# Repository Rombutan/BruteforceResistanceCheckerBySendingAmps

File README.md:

# BruteforceResistanceCheckerBySendingAmps

Want to measure small resistance things like fuses or wires? You can either spend days making some fancy amplifier or just pump a few amps through the thing you wanna measure and voila. That's what this project is.

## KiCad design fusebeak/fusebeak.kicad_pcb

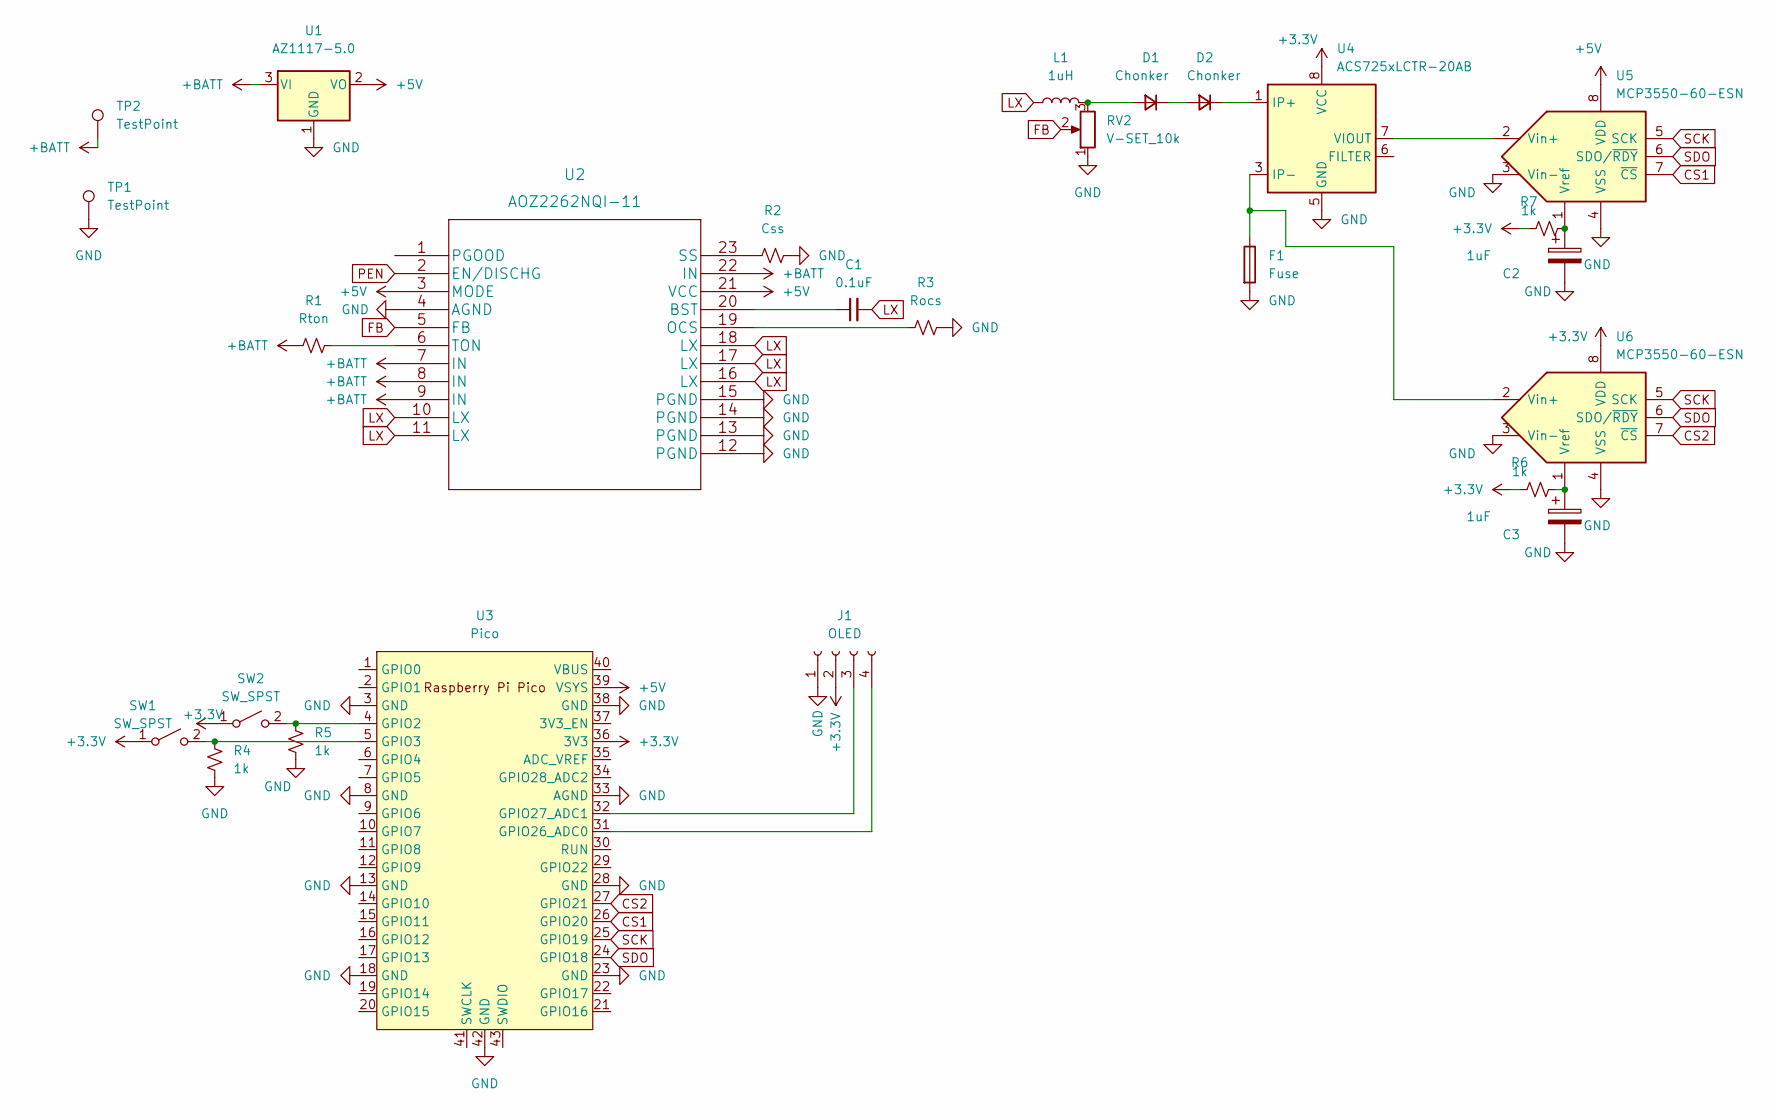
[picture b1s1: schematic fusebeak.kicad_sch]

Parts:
C1: 0.1uF; C_0402_1005Metric
C2, C3: 1uF; C_0402_1005Metric
D1, D2: Chonker; D_5KPW_P12.70mm_Horizontal
F1: Fuse; Fuseholder_Blade_ATO_Littelfuse_Pudenz_2_Pin
J1: OLED; PinHeader_1x04_P2.54mm_Vertical
L1: 1uH; L_7.3x7.3_H4.5
R1: Rton; R_0402_1005Metric
R2: Css; R_0402_1005Metric
R3: Rocs; R_0402_1005Metric
R4, R5, R6, R7: 1k; R_0402_1005Metric
RV2: V-SET_10k; Potentiometer_Bourns_3266Y_Vertical
SW1, SW2: SW_SPST; KSA_Tactile_SPST
TP1, TP2: TestPoint; TestPoint_Plated_Hole_D5.0mm
U1: AZ1117-5.0; SOT-223-3_TabPin2
U2: AOZ2262NQI-11
U3: Pico; RPi_Pico_SMD_TH
U4: ACS725xLCTR-20AB; SOIC-8_3.9x4.9mm_P1.27mm
U5, U6: MCP3550-60-ESN; SOIC-8-1EP_3.9x4.9mm_P1.27mm_EP2.29x3mm

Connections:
+3.3V: J1.2, R6.1, R7.1, SW1.1 (A), SW2.1 (A), U3.36 (3V3), U4.8 (VCC), U6.8 (VDD)
+5V: U1.2 (VO), U2.3 (MODE), U2.21 (VCC), U3.39 (VSYS), U5.8 (VDD)
+BATT: R1.1, TP2.1, U1.3 (VI), U2.7 (IN), U2.8 (IN), U2.9 (IN), U2.22 (IN)
CS1: U3.26 (GPIO20), U5.7 (~CS)
CS2: U3.27 (GPIO21), U6.7 (~CS)
FB: RV2.2, U2.5 (FB)
GND: C2.2, C3.2, F1.2, J1.1, R2.2, R3.2, R4.2, R5.2, RV2.1, TP1.1, U1.1 (GND), U2.4 (AGND), U2.12 (PGND), U2.13 (PGND), U2.14 (PGND), U2.15 (PGND), U3.3 (GND), U3.8 (GND), U3.13 (GND), U3.18 (GND), U3.23 (GND), U3.28 (GND), U3.33 (AGND), U3.38 (GND), U3.42 (GND), U4.5 (GND), U5.3 (Vin-), U5.4 (VSS), U6.3 (Vin-), U6.4 (VSS)
LX: C1.2, L1.1, U2.10 (LX), U2.11 (LX), U2.16 (LX), U2.17 (LX), U2.18 (LX)
unnamed: C1.1, U2.20 (BST)
unnamed: C2.1, R7.2, U5.1 (Vref)
unnamed: C3.1, R6.2, U6.1 (Vref)
unnamed: D1.1 (K), D2.2 (A)
unnamed: D1.2 (A), L1.2, RV2.3
unnamed: D2.1 (K), U4.1 (IP+), U4.2 (IP+)
unnamed: F1.1, U4.3 (IP-), U4.4 (IP-), U6.2 (Vin+)
unnamed: J1.3, U3.32 (GPIO27_ADC1)
unnamed: J1.4, U3.31 (GPIO26_ADC0)
unnamed: R1.2, U2.6 (TON)
unnamed: R2.1, U2.23 (SS)
unnamed: R3.1, U2.19 (OCS)
unnamed: R4.1, SW1.2 (B), U3.5 (GPIO3)
unnamed: R5.1, SW2.2 (B), U3.4 (GPIO2)
unnamed: U4.7 (VIOUT), U5.2 (Vin+)
PEN: U2.2 (EN/DISCHG)
SCK: U3.25 (GPIO19), U5.5 (SCK), U6.5 (SCK)
SDO: U3.24 (GPIO18), U5.6 (SDO/~RDY), U6.6 (SDO/~RDY)

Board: 2 copper layers, 26 parts (5 on the bottom side), 25 nets, no tracks yet.

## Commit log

2022-12-28 all the goofy from the last increment of the matrix

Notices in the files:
parts and their libraries:
Copyright 2021 Accelerated Designs. All rights reserved.
